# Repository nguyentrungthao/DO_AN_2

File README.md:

** I2C địa chỉ 0x44
- cấp nguồn ngoài
- reset ST

bug: - copy code ko đọc => nhầm bộ i2c 

**HC595

bug: đứt mạch nhầm chân giữa phần cứng và mền + chưa khóa led đc 

**encoder 

bug: chưa chạy liên tục được

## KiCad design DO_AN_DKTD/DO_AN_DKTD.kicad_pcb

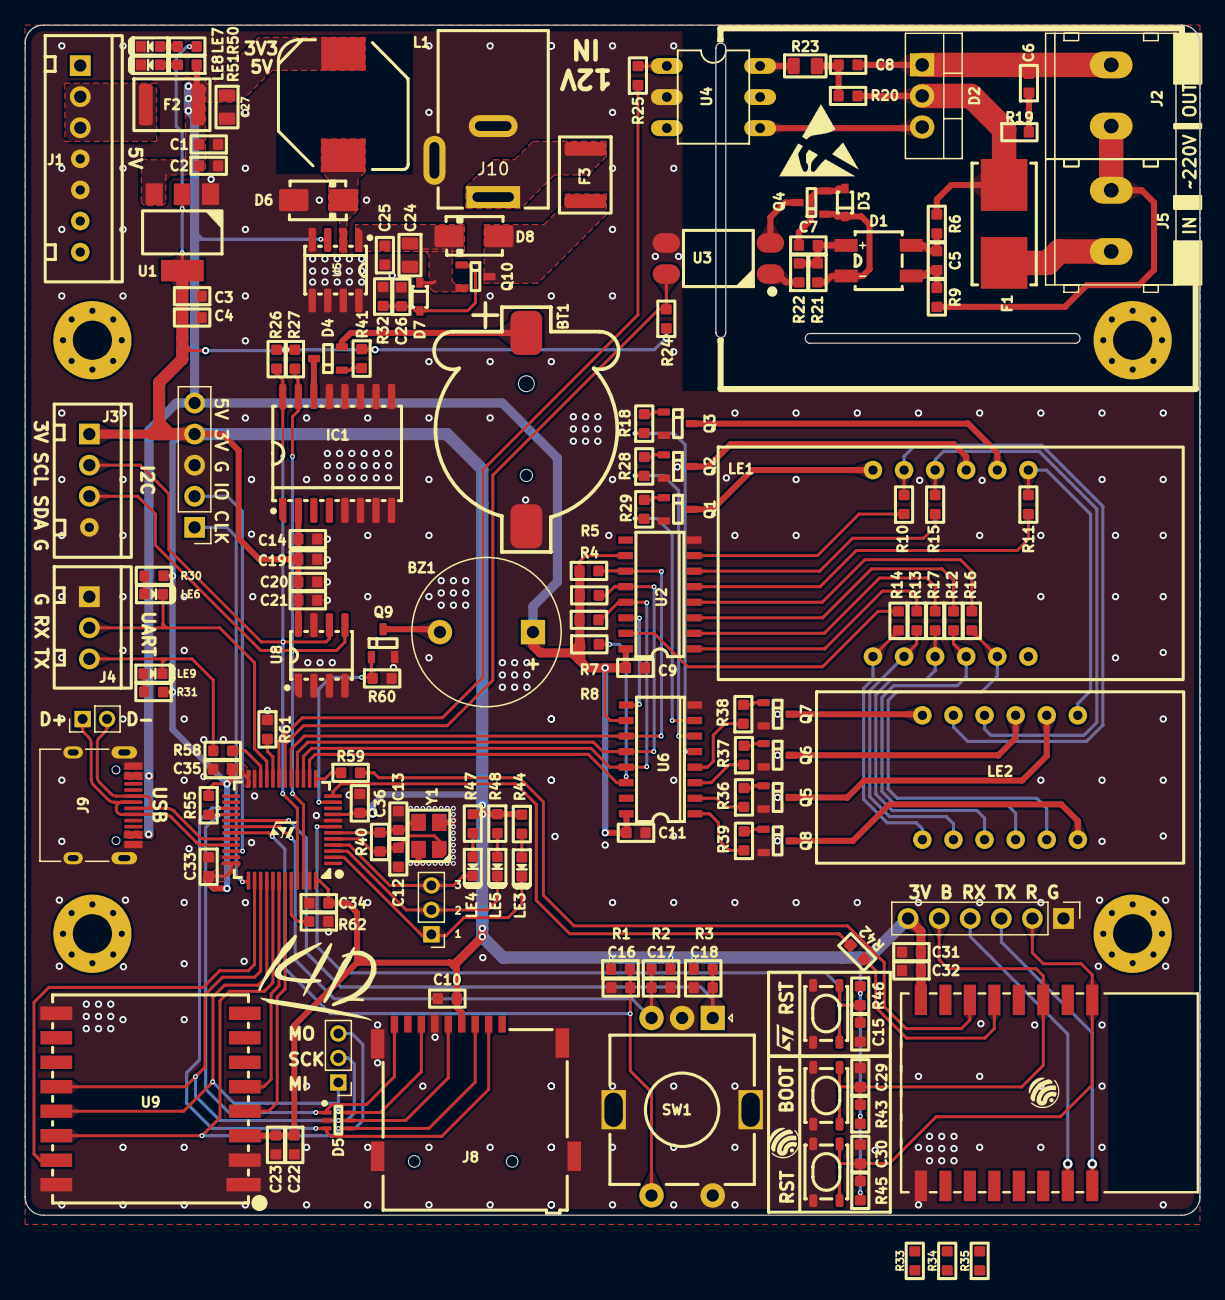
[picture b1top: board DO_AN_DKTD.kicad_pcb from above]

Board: 2 copper layers, 96.0 x 97.2 mm, 153 parts (0 on the bottom side), 120 nets.

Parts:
BT1: CR1220; BatteryHolder_CR1220
BZ1: Buzzer; Buzzer_12x9.5RM7.6
C1, C3, C15, C16, C17, C18, C22, C25, C29, C30, C31: 1uF; C_0603
C2, C4, C9, C10, C11, C19, C21, C23, C26, C32, C33, C34, C35, C36: 100nF; C_0603
C5, C6: 10nF; C_0603
C7, C14, C20: 10uF; C_0603
C8: 50nF; C_0603
C12, C13: 22pF; C_0603
C24, C27: 10uF; C_0805
D1: MB10F; Bridge_MB10F-13
D2: TRIAC; TO-220-3_Vertical
D3: 1N4148; D_SOD323
D4: BAT54C; SOT23-3
D5: SMF05C; TSSOP-6
D6, D8: SS54; D_SMA
D7: D_Schottky; D_SOD323
F1: Fuse; Fuseholder_Littelfuse_Nano2_154x
F2, F3: Fuse; Fuse_1812_4532Metric
IC1: RTC_DS3231M; SOIC-16W_7.5x10.3mm_P1.27mm
J1: Conn_01x07; Conn_XH-P2.54mm-7P
J2, J5: Conn_01x02; KF128-5.0-2P
J3: Conn_01x04; Conn_XH-P2.54mm-4P
J4: Conn_01x03; Conn_XH-P2.54mm-3P
J6: PinHeader_1x06_P2.54mm_Vertical
J7: Conn_01x05_Male; PinHeader_1x05_P2.54mm_Vertical
J8: Micro_SD_Card_Det1; MicroSD_Socket_9P
J9: USB_C_Receptacle; USB_C_Receptacle_XKB_U262-16XN-4BVC11
J10: Jack-DC; BarrelJack_Wuerth_6941xx301002
J11, J12: Conn_01x03_Pin; PinHeader_1x03_P2.00mm_Vertical
J13: Conn_01x02_Pin; PinHeader_1x02_P2.00mm_Vertical
L1: 68uH 2A; L_10.4x10.4_H4.8
LE1: 5631AS; 7Segment_4led_CC_38x19
LE2: 5631AS; 7Segment_4led_Cathode_30x14mm
LE3, LE4, LE5, LE6, LE7, LE8, LE9: Led; LED_0603
Q1, Q2, Q3, Q4, Q5, Q6, Q7, Q8: NPN; SOT23-3
Q9: N_Mosfet; SOT23-3
Q10: P_Mosfet; SOT23-3
R1, R2, R3, R4, R5, R7, R8, R26, R27, R55: 4k7; R_0603
R6, R9: 180k; R_0603
R10, R11, R12, R13, R14, R15, R16, R17, R22, R24, R30, R31, R41, R44, R47, R48, R50, R51: 1k; R_0603
R18, R28, R29, R36, R37, R38, R39: 2k; R_0603
R19: 39; R_0603
R20: 470; R_0603
R21: 22k; R_0603
R23: 360; R_0805
R25: 360; R_0603
R32: 12k; R_0603
R33, R34, R35, R43, R45, R46: 10k; R_0603
R40, R60: 1M; R_0603
R42: 100; R_0603
R58, R59: 100R; R_0603
R61, R62: 10K; R_0603
SW1: RotaryEncoder_Switch; RotaryEncoder_Alps_EC11E-Switch_Vertical_H20mm
SW2, SW3, SW4: SW_Push; SW_SPST_PTS810
U1: AMS1117; SOT233
U2, U6: 74HC595; SOIC-16W_3.92x10.2mm
U3: PC817; OPTO_SOT254P975X400-4N
U4: MOC3020M; DIL06-E
U5: XL1509; SOIC-8_3.9x4.9mm_P1.27mm
U7: STM32F103C8Tx; LQFP-48_7x7mm_P0.5mm
U8: 24C32N; SOIC-8_3.9x4.9mm_P1.27mm
U9: Ai-Thinker-Ra-02; MODULE_RA-02_LORA
U10: ESP-07; ESP8266-07__ESP32-C3-12F
Y1: Crystal_GND24_Small; Crystal_3225_4P_3.2x2.6mm

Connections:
+3V3: C3.2, C4.1, C10.2, C14.2, C19.2, C20.2, C21.2, C22.1, C23.1, C31.1, C32.1, C33.2, C34.2, C35.2, C36.2, IC1.2 (VCC), J3.1, J6.6, J7.4, J8.4 (VDD), R1.1, R2.1, R3.1, R24.1, R26.1, R27.1, R30.1, R31.1, R33.2, R34.2, R41.1, R43.1, R44.1, R45.1, R46.1, R47.1, R48.1, R50.1, R55.1, U1.2 (VO), U7.9 (VDDA), U7.24 (VDD), U7.36 (VDD), U7.48 (VDD), U8.8 (VCC), U9.3 (VDD), U10.8 (VCC)
+5V: BZ1.1 (-), C1.2, C2.1, C9.2, C11.2, C27.1, F2.2, J7.5, J9.A4 (VBUS), J9.A9 (VBUS), J9.B4 (VBUS), J9.B9 (VBUS), L1.2, R4.1, R5.1, R7.1, R8.1, R51.1, U1.3 (VI), U2.10 (~SRCLR), U2.16 (VCC), U5.3 (FB), U6.10 (~SRCLR), U6.16 (VCC)
/ESP/BOOT: C29.1, J6.5, R43.2, SW3.2, U10.18 (GPIO0)
/ESP/RST: C30.1, J6.2, R45.2, SW2.2, U10.1 (~RST)
/ESP/RX: J6.4, U10.21 (GPIO3/RXD)
/ESP/RX_ESP32: R42.2, U7.12 (PA2)
/ESP/TX: J6.3, U10.22 (GPIO1/TXD)
/ESP/TX_ESP32: R59.2, U10.6 (GPIO12)
/POWER/5vin: F2.1, J1.2, J1.3
/POWER/A: F3.1, J10.1
/POWER/B: D8.1, F3.2, Q10.3 (D)
/POWER/VOUT: D6.2, L1.1, U5.2 (OUTPUT)
/Peripheral/24C32.SCL: IC1.16 (SCL), J3.2, R26.2, U7.45 (PB8), U8.6 (SCL)
/Peripheral/24C32.SDA: IC1.15 (SDA), J3.3, R27.2, U7.46 (PB9), U8.5 (SDA)
/Peripheral/74HC595.OE: R7.2, U2.13 (~OE), U6.13 (~OE), U7.15 (PA5)
/Peripheral/74HC595.RCLK: R4.2, U2.12 (RCLK), U6.12 (RCLK), U7.16 (PA6)
/Peripheral/74HC595.SER: R8.2, U6.14 (SER), U7.14 (PA4)
/Peripheral/74HC595.SRCLK: R5.2, U2.11 (SRCLK), U6.11 (SRCLK), U7.17 (PA7)
/Peripheral/AC_DET: R24.2, U3.4, U7.18 (PB0)
/Peripheral/Buzzer: Q9.1 (G), R60.1, U7.11 (PA1)
/Peripheral/Encoder.EnC_A: C18.2, R3.2, SW1.A, U7.29 (PA8)
/Peripheral/Encoder.EnC_B: C17.2, R2.2, SW1.B, U7.30 (PA9)
/Peripheral/Encoder.EnC_BT: C16.2, R1.2, SW1.S1, U7.31 (PA10)
/Peripheral/L: F1.2, J5.1
/Peripheral/LE1: R29.1, U6.7 (QH)
/Peripheral/LE2: R28.1, U6.6 (QG)
/Peripheral/LE3: R18.1, U6.5 (QF)
/Peripheral/LE4: R38.1, U6.4 (QE)
/Peripheral/LE5: R37.1, U6.3 (QD)
/Peripheral/LE6: R36.1, U6.2 (QC)
/Peripheral/LE7: R39.1, U6.1 (QB)
/Peripheral/LOG_RX: J4.2, LE6.2, U7.21 (PB10)
/Peripheral/LOG_TX: J4.3, LE9.2, R58.1
/Peripheral/LORA.CS: U7.38 (PA15), U9.15 (~NSS)
/Peripheral/LORA.INT: U7.42 (PB6), U9.5 (DIO0)
/Peripheral/LORA.MISO: D5.6, J8.7 (DAT0), J12.1, U7.40 (PB4), U9.13 (MISO)
/Peripheral/LORA.MOSI: D5.4, J8.3 (CMD), J12.3, U7.41 (PB5), U9.14 (MOSI)
/Peripheral/LORA.RST: U7.43 (PB7), U9.4 (~RESET)
/Peripheral/LORA.SCK: D5.5, J8.5 (CLK), J12.2, U7.39 (PB3), U9.12 (SCK)
/Peripheral/L_after: D2.2 (A2), F1.1, R6.2, R19.1, R20.2
/Peripheral/Load: C6.2, C8.2, D2.1 (A1), J2.2
/Peripheral/N: J2.1, J5.2, R9.2
/Peripheral/SD.CS: D5.3, J8.2 (DAT3/CD), U7.27 (PB14)
/Peripheral/SD.DET: D5.1, J8.9 (DET), R55.2, U7.28 (PB15)
/Peripheral/TRIAC: R25.1, U7.19 (PB1)
/Peripheral/TYPE_C.D+: J9.A6 (D+), J9.B6 (D+), J13.1, U7.33 (PA12)
/Peripheral/TYPE_C.D-: J9.A7 (D-), J9.B7 (D-), J13.2, U7.32 (PA11)
/Peripheral/Vbat: BT1.1 (+), D4.2
/STM32/Led_test1: J11.1, LE3.2, U7.2 (PC13)
/STM32/Led_test2: J11.2, LE5.2, U7.3 (PC14)
/STM32/Led_test3: J11.3, LE4.2, U7.4 (PC15)
/STM32/PD0: C12.2, R40.1, U7.5 (PD0), Y1.1
/STM32/PD1: C13.1, R40.2, U7.6 (PD1), Y1.3
/STM32/RST: C15.1, R46.2, SW4.2, U7.7 (NRST)
/STM32/SWCLK: J7.1, U7.37 (PA14)
/STM32/SWDIO: J7.2, U7.34 (PA13)
GND: BT1.2 (-), C1.1, C2.2, C3.1, C4.2, C9.1, C10.1, C11.1, C12.1, C13.2, C14.1, C15.2, C16.1, C17.1, C18.1, C19.1, C20.1, C21.1, C22.2, C23.2, C24.2, C25.1, C26.2, C27.2, C29.2, C30.2, C31.2, C32.2, C33.1, C34.1, C35.1, C36.1, D5.2, D6.1, IC1.5 (GND), IC1.6 (GND), IC1.7 (GND), IC1.8 (GND), IC1.9 (GND), IC1.10 (GND), IC1.11 (GND), IC1.12 (GND), IC1.13 (GND), J1.4, J1.5, J3.4, J4.1, J6.1, J7.3, J8.6 (VSS), J8.10 (SHIELD), J9.A1 (GND), J9.A12 (GND), J9.B1 (GND), J9.B12 (GND), J9.S1 (SHIELD), J10.2, LE7.2, LE8.2, Q1.2 (E), Q2.2 (E), Q3.2 (E), Q5.2 (E), Q6.2 (E), Q7.2 (E), Q8.2 (E), Q9.2 (S), R32.2, R35.1, R60.2, R61.1, R62.1, SW1.C, SW1.MP (Shield), SW1.S2, SW2.1, SW3.1, SW4.1, U1.1 (GND), U2.8 (GND), U3.3, U4.2, U5.4 (ON/OFF), U5.5 (GND), U5.6 (GND), U5.7 (GND), U5.8 (GND), U6.8 (GND), U7.8 (VSSA), U7.23 (VSS), U7.35 (VSS), U7.47 (VSS), U8.1 (A0), U8.2 (A1), U8.3 (A2), U8.4 (GND), U8.7 (WP), U9.1 (GND), U9.2 (GND), U9.9 (GND), U9.16 (GND), U10.15 (GND), Y1.2, Y1.4
unnamed: D4.3, IC1.14 (VBAT)
unnamed: BZ1.2 (+), Q9.3 (D)
unnamed: C5.1, D1.4, R6.1
unnamed: C5.2, D1.2, R9.1
unnamed: C6.1, R19.2
unnamed: C8.1, R20.1, R23.2
unnamed: C7.1, D1.1 (+), R21.1, R22.2
unnamed: D1.3 (-), D3.2, Q4.1 (B), R21.2
unnamed: D2.3 (G), U4.4
unnamed: D4.1, R41.2
unnamed: LE1.12 (CC1), Q1.3 (C)
unnamed: LE1.9 (CC2), Q2.3 (C)
unnamed: LE1.8 (CC3), Q3.3 (C)
unnamed: LE1.3 (DPX), LE2.3 (DPX), R17.2
unnamed: LE1.11 (a), LE2.11 (a), R10.2
unnamed: LE1.7 (b), LE2.7 (b), R11.2
unnamed: LE1.4 (c), LE2.4 (c), R12.2
unnamed: LE1.2 (d), LE2.2 (d), R13.2
unnamed: LE1.1 (e), LE2.1 (e), R14.2
unnamed: LE1.10 (f), LE2.10 (f), R15.2
unnamed: LE1.5 (g), LE2.5 (g), R16.2
unnamed: LE2.12 (CC1), Q7.3 (C)
unnamed: LE2.9 (CC2), Q6.3 (C)
unnamed: LE2.8 (CC3), Q5.3 (C)
unnamed: LE2.6 (CC4), Q8.3 (C)
unnamed: LE3.1, R44.2
unnamed: LE4.1, R47.2
unnamed: LE5.1, R48.2
unnamed: LE6.1, R30.2
unnamed: LE7.1, R50.2
unnamed: LE8.1, R51.2
unnamed: LE9.1, R31.2
unnamed: Q1.1 (B), R29.2
unnamed: Q2.1 (B), R28.2
unnamed: Q3.1 (B), R18.2
unnamed: Q4.3 (C), U3.2
unnamed: C7.2, D3.1, Q4.2 (E)
unnamed: Q5.1 (B), R36.2
unnamed: Q6.1 (B), R37.2
unnamed: Q7.1 (B), R38.2
unnamed: Q8.1 (B), R39.2
unnamed: C26.1, D7.1, Q10.1 (G), R32.1
unnamed: R22.1, U3.1
unnamed: R23.1, U4.6
unnamed: R25.2, U4.1
unnamed: R14.1, U2.15 (QA)
unnamed: R13.1, U2.1 (QB)
unnamed: R17.1, U2.2 (QC)
unnamed: R12.1, U2.3 (QD)
unnamed: R16.1, U2.4 (QE)
unnamed: R11.1, U2.5 (QF)
unnamed: R15.1, U2.6 (QG)
unnamed: R10.1, U2.7 (QH)
unnamed: U2.14 (SER), U6.9 (QH')
unnamed: R62.2, U7.44 (BOOT0)
unnamed: R59.1, U7.13 (PA3)
unnamed: R61.2, U7.20 (PB2)
unnamed: R58.2, U7.22 (PB11)
unnamed: R33.1, U10.3 (EN)
unnamed: R34.1, U10.17 (GPIO2)
unnamed: R42.1, U10.5 (GPIO14)
unnamed: R35.2, U10.16 (GPIO15)
VDC: C24.1, C25.2, D7.2, D8.2, Q10.2 (S), U5.1 (VIN)

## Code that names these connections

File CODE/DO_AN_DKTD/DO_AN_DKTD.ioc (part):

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Mcu.Name=STM32F103C(8-B)Tx
Mcu.Package=LQFP48
Mcu.UserName=STM32F103C8Tx
PA10.GPIOParameters=GPIO_Label
PA10.GPIO_Label=EnC_BT
PA10.Signal=GPXTI10
PA11.Mode=Device
PA11.Signal=USB_DM
PA12.Mode=Device
PA12.Signal=USB_DP
PA13.Mode=Serial_Wire
PA13.Signal=SYS_JTMS-SWDIO
PA14.Mode=Serial_Wire
PA14.Signal=SYS_JTCK-SWCLK
PA15.GPIOParameters=GPIO_Speed,GPIO_Label
PA15.GPIO_Label=LORA_CS
PA15.GPIO_Speed=GPIO_SPEED_FREQ_HIGH
PA15.Signal=GPIO_Output
PA2.GPIOParameters=GPIO_Label
PA2.GPIO_Label=ESP_TX
PA2.Mode=Asynchronous
PA2.Signal=USART2_TX
PA3.GPIOParameters=GPIO_Label
PA3.GPIO_Label=ESP_RX
PA3.Mode=Asynchronous
PA3.Signal=USART2_RX
PA4.GPIOParameters=GPIO_Speed,GPIO_PuPd,GPIO_Label,GPIO_ModeDefaultOutputPP
PA4.GPIO_Label=SER
PA4.GPIO_ModeDefaultOutputPP=GPIO_MODE_OUTPUT_OD
PA4.GPIO_PuPd=GPIO_NOPULL
PA4.GPIO_Speed=GPIO_SPEED_FREQ_HIGH
PA4.Signal=GPIO_Output
PA5.GPIOParameters=GPIO_Speed,GPIO_PuPd,GPIO_Label,GPIO_ModeDefaultOutputPP
PA5.GPIO_Label=OE
PA5.GPIO_ModeDefaultOutputPP=GPIO_MODE_OUTPUT_OD
PA5.GPIO_PuPd=GPIO_NOPULL
PA5.GPIO_Speed=GPIO_SPEED_FREQ_HIGH
PA5.Signal=GPIO_Output
PA6.GPIOParameters=GPIO_Speed,GPIO_PuPd,GPIO_Label,GPIO_ModeDefaultOutputPP
PA6.GPIO_Label=RLCK
PA6.GPIO_ModeDefaultOutputPP=GPIO_MODE_OUTPUT_OD
PA6.GPIO_PuPd=GPIO_NOPULL
PA6.GPIO_Speed=GPIO_SPEED_FREQ_HIGH
PA6.Signal=GPIO_Output
PA7.GPIOParameters=GPIO_Speed,GPIO_PuPd,GPIO_Label,GPIO_ModeDefaultOutputPP
PA7.GPIO_Label=SRCLK
PA7.GPIO_ModeDefaultOutputPP=GPIO_MODE_OUTPUT_OD
PA7.GPIO_PuPd=GPIO_NOPULL
PA7.GPIO_Speed=GPIO_SPEED_FREQ_HIGH
PA7.Signal=GPIO_Output
PA8.Signal=S_TIM1_CH1
PA9.Signal=S_TIM1_CH2
PB0.GPIOParameters=GPIO_Label,GPIO_ModeDefaultEXTI
PB0.GPIO_Label=ACDET
PB0.GPIO_ModeDefaultEXTI=GPIO_MODE_IT_FALLING
PB0.Signal=GPXTI0
PB1.GPIOParameters=GPIO_Speed,GPIO_Label
PB1.GPIO_Label=TRIAC
PB1.GPIO_Speed=GPIO_SPEED_FREQ_HIGH
PB1.Signal=GPIO_Output
PB10.GPIOParameters=GPIO_Label
PB10.GPIO_Label=LOG_TX
PB10.Mode=Asynchronous
PB10.Signal=USART3_TX
PB11.GPIOParameters=GPIO_Label
PB11.GPIO_Label=LOG_RX
PB11.Mode=Asynchronous
PB11.Signal=USART3_RX
PB14.GPIOParameters=GPIO_Speed,GPIO_Label
PB14.GPIO_Label=SD_CS
PB14.GPIO_Speed=GPIO_SPEED_FREQ_HIGH
PB14.Signal=GPIO_Output
PB15.GPIOParameters=GPIO_Label
PB15.GPIO_Label=SD_DET
PB15.Signal=GPXTI15
PB3.GPIOParameters=GPIO_Label
PB3.GPIO_Label=LORA_SCK
PB3.Mode=Full_Duplex_Master
PB3.Signal=SPI1_SCK
PB4.GPIOParameters=GPIO_Label
PB4.GPIO_Label=LORA_MISO
PB4.Mode=Full_Duplex_Master
PB4.Signal=SPI1_MISO
PB5.GPIOParameters=GPIO_Label
PB5.GPIO_Label=LORA_MOSI
PB5.Mode=Full_Duplex_Master
PB5.Signal=SPI1_MOSI
PB6.GPIOParameters=GPIO_Label
PB6.GPIO_Label=LORA_INT
PB6.Signal=GPXTI6
PB7.GPIOParameters=GPIO_Speed,GPIO_Label
PB7.GPIO_Label=LORA_RST
PB7.GPIO_Speed=GPIO_SPEED_FREQ_HIGH
PB7.Signal=GPIO_Output
PB8.Mode=I2C
PB8.Signal=I2C1_SCL
PB9.Mode=I2C
PB9.Signal=I2C1_SDA
PC13-TAMPER-RTC.GPIOParameters=GPIO_Speed,GPIO_Label
PC13-TAMPER-RTC.GPIO_Label=Led_test1
PC13-TAMPER-RTC.GPIO_Speed=GPIO_SPEED_FREQ_HIGH
PC13-TAMPER-RTC.Signal=GPIO_Output
PC14-OSC32_IN.GPIOParameters=GPIO_Speed,GPIO_Label
PC14-OSC32_IN.GPIO_Label=Led_test2
PC14-OSC32_IN.GPIO_Speed=GPIO_SPEED_FREQ_HIGH
PC14-OSC32_IN.Signal=GPIO_Output
PC15-OSC32_OUT.GPIOParameters=GPIO_Speed,GPIO_Label
PC15-OSC32_OUT.GPIO_Label=Led_test3
PC15-OSC32_OUT.GPIO_Speed=GPIO_SPEED_FREQ_HIGH
PC15-OSC32_OUT.Signal=GPIO_Output
PD0-OSC_IN.Mode=HSE-External-Oscillator
PD0-OSC_IN.Signal=RCC_OSC_IN
PD1-OSC_OUT.Mode=HSE-External-Oscillator
PD1-OSC_OUT.Signal=RCC_OSC_OUT
RCC.SYSCLKFreq_VALUE=72000000
RCC.SYSCLKSource=RCC_SYSCLKSOURCE_PLLCLK
board=custom

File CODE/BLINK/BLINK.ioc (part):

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Mcu.Name=STM32F103C(8-B)Tx
Mcu.Package=LQFP48
Mcu.UserName=STM32F103C8Tx
PA1.GPIOParameters=GPIO_Speed,GPIO_Label
PA1.GPIO_Label=BUZZER
PA1.GPIO_Speed=GPIO_SPEED_FREQ_HIGH
PA1.Signal=GPIO_Output
PA13.Mode=Serial_Wire
PA13.Signal=SYS_JTMS-SWDIO
PA14.Mode=Serial_Wire
PA14.Signal=SYS_JTCK-SWCLK
PB1.GPIOParameters=GPIO_Speed,GPIO_Label
PB1.GPIO_Label=TRIAC
PB1.GPIO_Speed=GPIO_SPEED_FREQ_HIGH
PB1.Signal=GPIO_Output
PC13-TAMPER-RTC.GPIOParameters=GPIO_Speed,PinState,GPIO_Label
PC13-TAMPER-RTC.GPIO_Label=LED1
PC13-TAMPER-RTC.GPIO_Speed=GPIO_SPEED_FREQ_HIGH
PC13-TAMPER-RTC.PinState=GPIO_PIN_SET
PC13-TAMPER-RTC.Signal=GPIO_Output
PC14-OSC32_IN.GPIOParameters=GPIO_Speed,GPIO_Label
PC14-OSC32_IN.GPIO_Label=LED2
PC14-OSC32_IN.GPIO_Speed=GPIO_SPEED_FREQ_HIGH
PC14-OSC32_IN.Signal=GPIO_Output
PC15-OSC32_OUT.GPIOParameters=GPIO_Speed,GPIO_Label
PC15-OSC32_OUT.GPIO_Label=LED3
PC15-OSC32_OUT.GPIO_Speed=GPIO_SPEED_FREQ_HIGH
PC15-OSC32_OUT.Signal=GPIO_Output
PD0-OSC_IN.Mode=HSE-External-Oscillator
PD0-OSC_IN.Signal=RCC_OSC_IN
PD1-OSC_OUT.Mode=HSE-External-Oscillator
PD1-OSC_OUT.Signal=RCC_OSC_OUT
RCC.SYSCLKFreq_VALUE=72000000
RCC.SYSCLKSource=RCC_SYSCLKSOURCE_PLLCLK
board=custom

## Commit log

2023-04-11 code update
2023-04-14 completed layout PCB Ver 1.0
2023-04-15 add testoint SPI USB LEDTEST and Buck power
2023-04-17 commit to change branch
2023-04-21 config pin STM32 CubeIDE, and add resistor ESP8266
2023-04-23 comlete read temperature and scan 7 segment
2023-05-15 complete code DO_AN_MON

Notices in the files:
parts and their libraries:
Copyright 2021 Accelerated Designs. All rights reserved.
